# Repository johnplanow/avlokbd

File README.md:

# Avlo44 Keyboard

Avlo44 is a 6x3+4 column-staggered, split, unibody keyboard. 

Inspired by the [Kyria](https://blog.splitkb.com/blog/introducing-the-kyria), 
[Reviung41](https://github.com/gtips/reviung) and [Lily58](https://github.com/kata0510/Lily58), it was designed with the following goals in mind:

* **Goal**: Easy to carry around the office with my laptop when I have meetings.
  * *Choice*: Unibody design. I like split keyboards, but they can be awkward to pick up and carry around.
  * *Choice*: Wireless. I intend to install a [nice!nano](https://nicekeyboards.com/nice-nano/) on the board eventually.
* **Goal**: Minimize keymap customization and learning curve for everyday office work and programming.<sup>1</sup>
  * *Corollary*: This means 3x6 with dedicated keys for all Mac modifiers. I don't find a worthwhile tradeoff in fewer keys.
  * *Choice*: 44 keys in a 6x3+4 layout.
* **Goal**: Experiment with an aggressive column-stagger, especially for the pinky. This seems intuitive to me, given my pinky is significantly shorter than other fingers.
  * *Choice*: The column-stagger is lifted directly from the [Kyria](https://blog.splitkb.com/blog/introducing-the-kyria). All credit to [Thomas Baart](https://thomasbaart.nl/) for its design.
* **Goal**: Ease of assembly
  * *Choice*: Through-hole diodes were used instead of surface-mount. Initial revisions still have surface-mount LEDs because I didn't care enough about backlighting to invest additional effort into them.
* **Goal**: Fun stuff!
  * *Choice*: I included an OLED, which has always been more fun than functional for me, because it's relatively easy. I will probably add a rotary encoder in a follow-up revision.

Future plans:
* 4x6 variant:
  * I have a PC used mostly for gaming. I'd like a dedicated number row for this<sup>1</sup> paired with the aggressive column-stagger.
* Breakaway sixth columns (for a 3x5 variant), as requested by someone when I first posted the Avlo44.
* Choc switch support, as requested by someone when I first posted the Avlo44.
* As mentioned above, I'd like to experiment with a rotary encoder.

## Footnotes

<sup>1</sup> In my experience, there is an inflection point as one reduces the number of keys, where there is a drastic increase in the complexity of keymap customizations (combos, layers, mod-taps, etc.) I think this inflection point depends on application: general office work versus programming versus gaming. In all cases, moving beyond it requires significantly more time/energy to adapt, tune, etc.

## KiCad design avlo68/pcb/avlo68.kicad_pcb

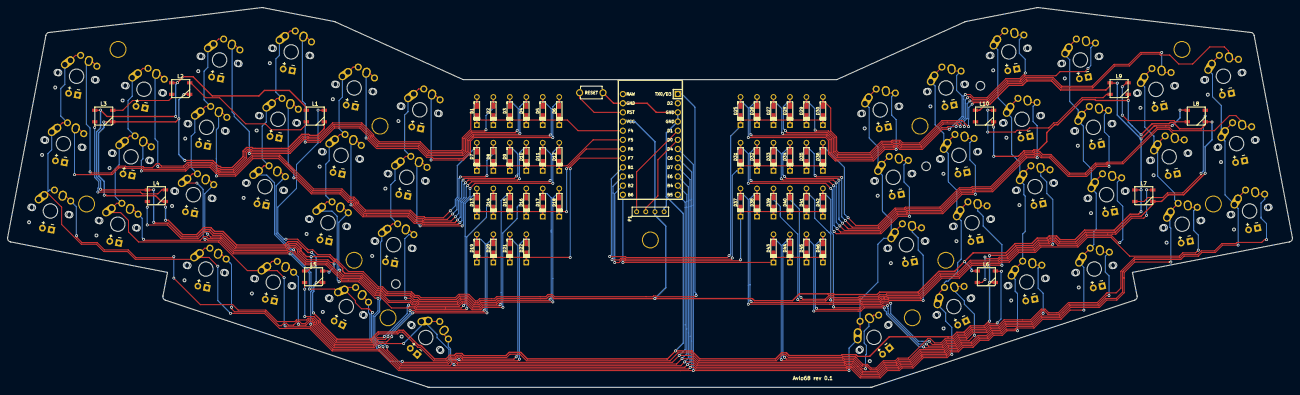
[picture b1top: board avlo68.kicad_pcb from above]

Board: 2 copper layers, 356.5 x 105.4 mm, 112 parts (1 on the bottom side), 73 nets.

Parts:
D1, D2, D3, D4, D5, D6, D7, D8, D9, D10, D11, D12, D13, D14, D15, D16, D17, D18, D19, D20, D21, D22, D25, D26, D27, D28, D29, D30, D31, D32, D33, D34, D35, D36, D37, D38, D39, D40, D41, D42, D43, D44, D45, D46: 1N4148W; Diode-dual
L1, L2, L3, L4, L5, L6, L7, L8, L9, L10: WS2812B
P1: OLED; OLED_4Pin
RESET1: SW_PUSH; TACT_SWITCH_TVBP06
SW1, SW2, SW3, SW4, SW5, SW6, SW7, SW8, SW9, SW10, SW11, SW12, SW13, SW14, SW15, SW16, SW17, SW18, SW19, SW20, SW21, SW22, SW25, SW26, SW27, SW28, SW29, SW30, SW31, SW32, SW33, SW34, SW35, SW36, SW37, SW38, SW39, SW40, SW41, SW42, SW43, SW44, SW45, SW46: SW_PUSH; MX-Alps-Choc-1U
TH1, TH2, TH3, TH4, TH5, TH6, TH7, TH8, TH9, TH10, TH11: HOLE; HOLE_M2_TH
U1: ProMicro; ArduinoProMicro

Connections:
GND: L1.3, L2.3, L3.3, L4.3, L5.3, L6.3, L7.3, L8.3, L9.3, L10.3, P1.4, RESET1.2, U1.3, U1.4, U1.23
LED: L1.4, U1.1
unnamed: D1.2, SW1.2
unnamed: D2.2, SW2.2
unnamed: D3.2, SW3.2
unnamed: D4.2, SW4.2
unnamed: D5.2, SW5.2
unnamed: D6.2, SW6.2
unnamed: D7.2, SW7.2
unnamed: D8.2, SW8.2
unnamed: D9.2, SW9.2
unnamed: D10.2, SW10.2
unnamed: D11.2, SW11.2
unnamed: D12.2, SW12.2
unnamed: D13.2, SW13.2
unnamed: D14.2, SW14.2
unnamed: D15.2, SW15.2
unnamed: D16.2, SW16.2
unnamed: D17.2, SW17.2
unnamed: D18.2, SW18.2
unnamed: D19.2, SW19.2
unnamed: D20.2, SW20.2
unnamed: D21.2, SW21.2
unnamed: D22.2, SW22.2
unnamed: D25.2, SW25.2
unnamed: D26.2, SW26.2
unnamed: D27.2, SW27.2
unnamed: D28.2, SW28.2
unnamed: D29.2, SW29.2
unnamed: D30.2, SW30.2
unnamed: D31.2, SW31.2
unnamed: D32.2, SW32.2
unnamed: D33.2, SW33.2
unnamed: D34.2, SW34.2
unnamed: D35.2, SW35.2
unnamed: D36.2, SW36.2
unnamed: D37.2, SW37.2
unnamed: D38.2, SW38.2
unnamed: D39.2, SW39.2
unnamed: D40.2, SW40.2
unnamed: D41.2, SW41.2
unnamed: D42.2, SW42.2
unnamed: D43.2, SW43.2
unnamed: D44.2, SW44.2
unnamed: D45.2, SW45.2
unnamed: D46.2, SW46.2
unnamed: L1.2, L2.4
unnamed: L2.2, L3.4
unnamed: L3.2, L4.4
unnamed: L4.2, L5.4
unnamed: L5.2, L6.4
unnamed: L6.2, L7.4
unnamed: L7.2, L8.4
unnamed: L8.2, L9.4
unnamed: L9.2, L10.4
SCL: P1.2, U1.6
SDA: P1.1, U1.5
VCC: L1.1, L2.1, L3.1, L4.1, L5.1, L6.1, L7.1, L8.1, L9.1, L10.1, P1.3, U1.21
col0: SW1.1, SW7.1, SW13.1, SW19.1, SW25.1, SW31.1, SW37.1, SW43.1, U1.7
col1: SW2.1, SW8.1, SW14.1, SW20.1, SW26.1, SW32.1, SW38.1, SW44.1, U1.8
col2: SW3.1, SW9.1, SW15.1, SW21.1, SW27.1, SW33.1, SW39.1, SW45.1, U1.9
col3: SW4.1, SW10.1, SW16.1, SW22.1, SW28.1, SW34.1, SW40.1, SW46.1, U1.10
col4: SW5.1, SW11.1, SW17.1, SW29.1, SW35.1, SW41.1, U1.11
col5: SW6.1, SW12.1, SW18.1, SW30.1, SW36.1, SW42.1, U1.12
reset: RESET1.1, U1.22
row0: D1.1, D2.1, D3.1, D4.1, D5.1, D6.1, U1.20
row1: D7.1, D8.1, D9.1, D10.1, D11.1, D12.1, U1.19
row2: D13.1, D14.1, D15.1, D16.1, D17.1, D18.1, U1.18
row3: D19.1, D20.1, D21.1, D22.1, U1.17
row4: D25.1, D26.1, D27.1, D28.1, D29.1, D30.1, U1.16
row5: D31.1, D32.1, D33.1, D34.1, D35.1, D36.1, U1.15
row6: D37.1, D38.1, D39.1, D40.1, D41.1, D42.1, U1.14
row7: D43.1, D44.1, D45.1, D46.1, U1.13

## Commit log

2021-05-16 Add PCB for Avlo44 with initial routing for left half
2021-05-16 Initial routing complete for Avlo44
2021-05-16 Add gitignore and bottom plate
2021-05-16 Add board outline for Avlo44
2021-05-18 Update mounting holes, add artwork and add production files
2021-05-18 Add README
2021-06-02 Fix missing trace and add switch footprint for Kailh socket
2021-07-22 Add Avlo44 rev0.1 images
2021-07-22 Add images to README
2021-07-22 Add notes on future plans
2022-06-05 Duplicate avlo44 project for avlo68. Update matrix schematic.
2022-06-05 Add Black Pill footprint and schematic. Drop Black Pill onto avlo68 schematic.
2022-06-12 Add rotary encoders and OLED to schematic
